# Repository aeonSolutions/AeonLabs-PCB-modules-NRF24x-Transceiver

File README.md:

# AeonLabs PCB modules NRF24x Transceiver
This is a pcb design module for a  Nordic NRF24x Tranceiver 2.4Ghz. Suitable as a add-on design for any other KiCad project.

*Don't forget to LIKE , SHARE and subscribe the free whatsApp group* and if you liked this PCB consider buying me a cup of coffee. Links below.

### Status
  Waiting for first batch from factory. Not tested.

If you already tested this PCB send me a message. Thank you

## Revisions
- revision 1.0
 
## Download options
Download this repository if you need the KiCad Files or, download the Gerber files in the release section of this repository

## Liked it ? Get a Free PCB for yourself
Send me your Device or hardware and i will design a custom PCB for it. Free of charge. Contact-me on WhatsApp or email for more info. 

## Q&A WhatsApp Group
If you have any Questions or simply  like this kind of projects and want to stay updated with the latest research ideas and prototypes during the day and week, join the WhatsApp Group
[A.I. Things](https://chat.whatsapp.com/FkNC7u83kuy2QRA5sqjBVg)

## Fully assembled PCB
Alternatively, and if you do not want to build a PCB by yourself and like to buy one, you can do it here:

The price will be around 30eur plus postage fees.
(I will also deliver the assembled PCB with all the components in place at a fair aditonal cost).

This PCB is a #direct fit #replacement of the one found on the internet at sale. For example here: https://s.click.aliexpress.com/e/_9wRPxz

#### Be supportive of my dedication and work towards technology education and buy me a coffee. Link below.

________________________________________________________________________________________________________________

## PCB Parts list
- [Capacitor SMD 0805](https://s.click.aliexpress.com/e/_AVdmzr)
- [Resistor SMD 1206 ](https://s.click.aliexpress.com/e/_A7OXrR)
- [NRF2401](https://s.click.aliexpress.com/e/_Dnd4nBd)
- [SMD Crystal](https://s.click.aliexpress.com/e/_DFLqC6r)
- [SMD Inductor](https://s.click.aliexpress.com/e/_DcYwfdh)

## Firmware Download 
one can use the PCB in the repository [AeonLabs-MCU-Burner-USB-to-UART-TTL](https://github.com/aeonSolutions/AeonLabs-MCU-Burner-USB-to-UART-TTL) to program the ESP32 WROOM32 MCU on this PCB.

______________________________________________________________________________________________________________________________

### License
2022 Creative Commons Attribution-NonCommercial-ShareAlike 4.0 International

https://creativecommons.org/licenses/by-nc-sa/4.0/

### Own a copy of this work
if you like to own a copy of this work, you can buy it as a NFT or Ethereum. contact me for more details at mtpsilva@gmail.com
________________________________________________________________________________________________________________
## [Go back to main catalogue page](https://github.com/aeonSolutions/PCB-Prototyping-Catalogue)
________________________________________________________________________________________________________________

### Share this PCB board files

### PCB Fabrication

______________________________________________________________________________________________________________________________

### Be supportive of my dedication and work towards technology education and buy me a cup of coffee
Buy me a cup of coffee, a slice of pizza or a book to help me study, eat and think new PCB design files.

### Make a donation on Paypal
Make a donation on paypal and get a TAX refund*.

### Support all these open hardware projects and become a patreon  
I will give a free PCB design in KiCad to all patreon supporters. To learn more go to patreon.com. Link below.

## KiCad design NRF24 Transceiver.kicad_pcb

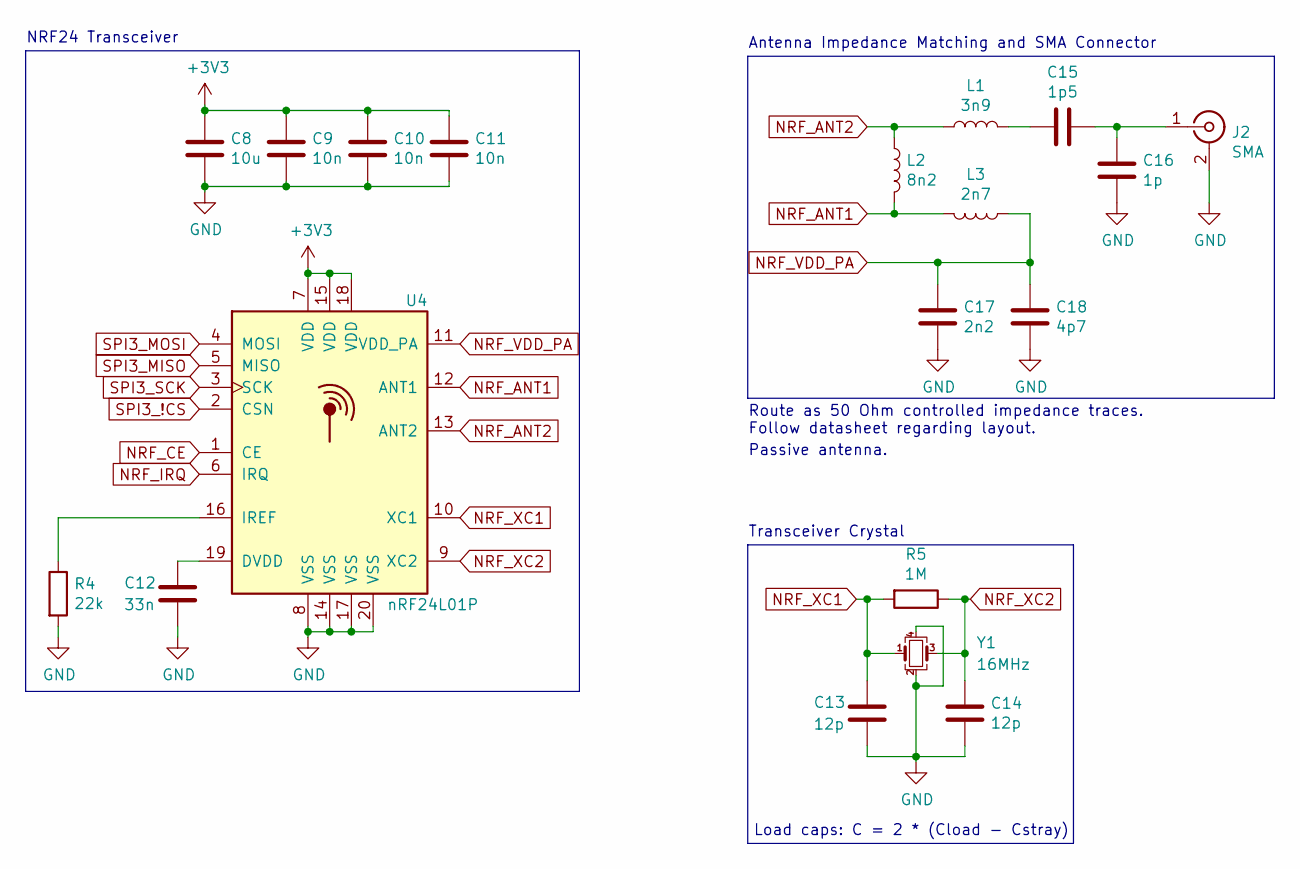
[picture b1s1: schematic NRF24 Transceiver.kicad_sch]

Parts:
C8: 10u; C_0805_2012Metric
C9, C10, C11: 10n; C_0805_2012Metric
C12: 33n; C_0805_2012Metric
C13, C14: 12p; C_0805_2012Metric
C15: 1p5; C_0805_2012Metric
C16: 1p; C_0805_2012Metric
C17: 2n2; C_0805_2012Metric
C18: 4p7; C_0805_2012Metric
J2: SMA; SMA_Samtec_SMA-J-P-X-ST-EM1_EdgeMount
L1: 3n9; L_0805_2012Metric
L2: 8n2; L_0805_2012Metric
L3: 2n7; L_0805_2012Metric
R4: 22k; R_0805_2012Metric
R5: 1M; R_0805_2012Metric
U4: nRF24L01P; QFN-20-1EP_4x4mm_P0.5mm_EP2.5x2.5mm
Y1: 16MHz; Crystal_SMD_3225-4Pin_3.2x2.5mm

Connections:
+3V3: C8.1, C9.1, C10.1, C11.1, U4.7 (VDD), U4.15 (VDD), U4.18 (VDD)
GND: C8.2, C9.2, C10.2, C11.2, C12.2, C13.2, C14.2, C16.1, C17.1, C18.1, J2.2 (Ext), R4.2, U4.8 (VSS), U4.14 (VSS), U4.17 (VSS), U4.20 (VSS), Y1.2, Y1.4
NRF_ANT1: L2.2, L3.2, U4.12 (ANT1)
NRF_ANT2: L1.1, L2.1, U4.13 (ANT2)
NRF_CE: U4.1 (CE)
NRF_IRQ: U4.6 (IRQ)
NRF_VDD_PA: C17.2, C18.2, L3.1, U4.11 (VDD_PA)
NRF_XC1: C13.1, R5.2, U4.10 (XC1), Y1.1
NRF_XC2: C14.1, R5.1, U4.9 (XC2), Y1.3
unnamed: C12.1, U4.19 (DVDD)
unnamed: C15.1, C16.2, J2.1 (In)
unnamed: C15.2, L1.2
unnamed: R4.1, U4.16 (IREF)
SPI3_!CS: U4.2 (CSN)
SPI3_MISO: U4.5 (MISO)
SPI3_MOSI: U4.4 (MOSI)
SPI3_SCK: U4.3 (SCK)

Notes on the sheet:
Route as 50 Ohm controlled impedance traces. Follow datasheet regarding layout.
Load caps: C = 2 * (Cload - Cstray)
Transceiver Crystal
NRF24 Transceiver
Passive antenna.
Antenna Impedance Matching and SMA Connector

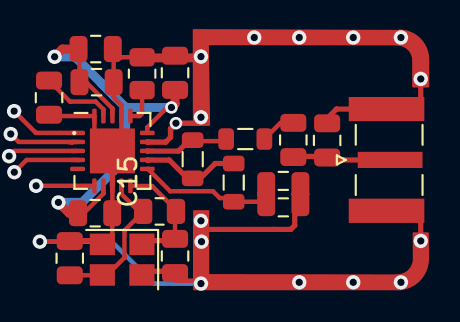
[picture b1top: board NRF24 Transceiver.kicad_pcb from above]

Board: 2 copper layers, 19 parts (0 on the bottom side), 11 nets.

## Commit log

2022-07-17 rev. 1.0
